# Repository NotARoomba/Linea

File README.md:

<h1 align="center">
  <br>
  
  <br>
  Linea
  <br>
</h1>

<h4 align="center">
Project files for a custom EMR tablet from scratch.

Inspired by [Project Patchouli](https://gitlab.com/yukidama/patchouli).

</h4>

<div align="center">

</div>

<p align="center">
  <a href="#key-features">Key Features</a> •
  <a href="#case-and-cad">Case & CAD</a> •
  <a href="#pcb">PCB</a> •
  <a href="#bom">BOM</a> •
  <a href="#credits">Credits</a> •
  <a href="#license">License</a>
</p>

<!---

--->

## Key Features

- ~500kHz scanning rate
- Large (170x110mm) drawing area
- Bluetooth support (via STM32)
- USB-C for data and charging
- ~~Pen~~ (for another version)

## Case and CAD

The case includes:

- 3D printed parts: a base and a top cover
- Snap-fit case

Designed in Fusion 360.

## PCB

Designed in KiCad. Notable points:

- STM32WB55RGV6TR for bluetooth support
- LiPo battery charging circuit
- USB-C
- 2 ground planes
- FPC touchpad

The PCB has 2 components, the FPC coil grid and the main board.

### FPC

### Main Board

## BOM

| Item         | Price (USD) | Source                                                                                                                                                                                                                                                                                                                                                                                                                                                          |
| ------------ | ----------- | --------------------------------------------------------------------------------------------------------------------------------------------------------------------------------------------------------------------------------------------------------------------------------------------------------------------------------------------------------------------------------------------------------------------------------------------------------------- |
| FPC Board    | 48.67       | JLCPCB                                                                                                                                                                                                                                                                                                                                                                                                                                                          |
| Main Board   | 207.14      | JLCPCB                                                                                                                                                                                                                                                                                                                                                                                                                                                          |
| Test Pen     | 12.35       | [Aliexpress](https://www.aliexpress.com/item/1005001860233195.html?spm=a2g0o.productlist.0.0.111a75d5sBjHGs&mp=1&pdp_npi=5%40dis%21COP%21COP%2077314.30%21COP%2049500.76%21%21COP%2049500.76%21%21%21%40210337bc17525387622585637ecb2a%2112000017887624552%21ct%21CO%216414363499%21%211%210) |
| LiPo 1200mAh | 12.00       | [Online Marketplace](https://articulo.mercadolibre.com.co/MCO-897219547-bateria-37v-1200mah-litio-lipo-35-x-6cm-ancho-05cm-_JM#polycard_client=search-nordic&position=31&search_layout=stack&type=item&tracking_id=64c5a1d6-adab-4203-b581-c1839af5c176&wid=MCO897219547&sid=search)                                                                                                                                                                            |
| **Subtotal** | 280.16      |                                                                                                                                                                                                                                                                                                                                                                                                                                                                 |
| **Shipping** | 30.00       | Estimated                                                                                                                                                                                                                                                                                                                                                                                                                                                       |
| **Total**    | 310.16      |                                                                                                                                                                                                                                                                                                                                                                                                                                                                 |

<!-- https://articulo.mercadolibre.com.co/MCO-568567056-lapiz-repuesto-tabla-digitalizadora-xp-pen-p03-no-wacom-_JM?searchVariation=176600496495#is_advertising=true&searchVariation=176600496495&backend_model=search-backend&position=8&search_layout=stack&type=pad&tracking_id=9f203117-ca3d-40ac-bdf1-dadf37d1ff62&is_advertising=true&ad_domain=VQCATCORE_LST&ad_position=8&ad_click_id=YjFjZWVmY2UtZGUwNi00Y2Y4LTk2NDktMmQ1NjNhZGUyMzNj -->

## Credits

- [Project Patchouli](https://gitlab.com/yukidama/patchouli)
- [Flipper Zero](https://docs.flipper.net/development/hardware)
- Check `/references` for more information

This project uses:

- [KiCad](https://www.kicad.org/)
- [STM32MX](https://www.st.com/en/development-tools/stm32cubemx.html)
- [Fusion 360](https://www.autodesk.com/products/fusion-360/overview)

## You may also like...

- [Niveles De Niveles](https://github.com/NotARoomba/NivelesDeNiveles) – Real-time flood alert app
- [ROCKETMEN](https://github.com/NotARoomba/ROCKETMEN) – Custom flight controller files
- [Tamaki](https://github.com/NotARoomba/Tamaki) – A cute HackPad

## License

MIT

---

> [notaroomba.dev](https://notaroomba.dev) &nbsp;&middot;&nbsp;
> GitHub [@NotARoomba](https://github.com/NotARoomba)

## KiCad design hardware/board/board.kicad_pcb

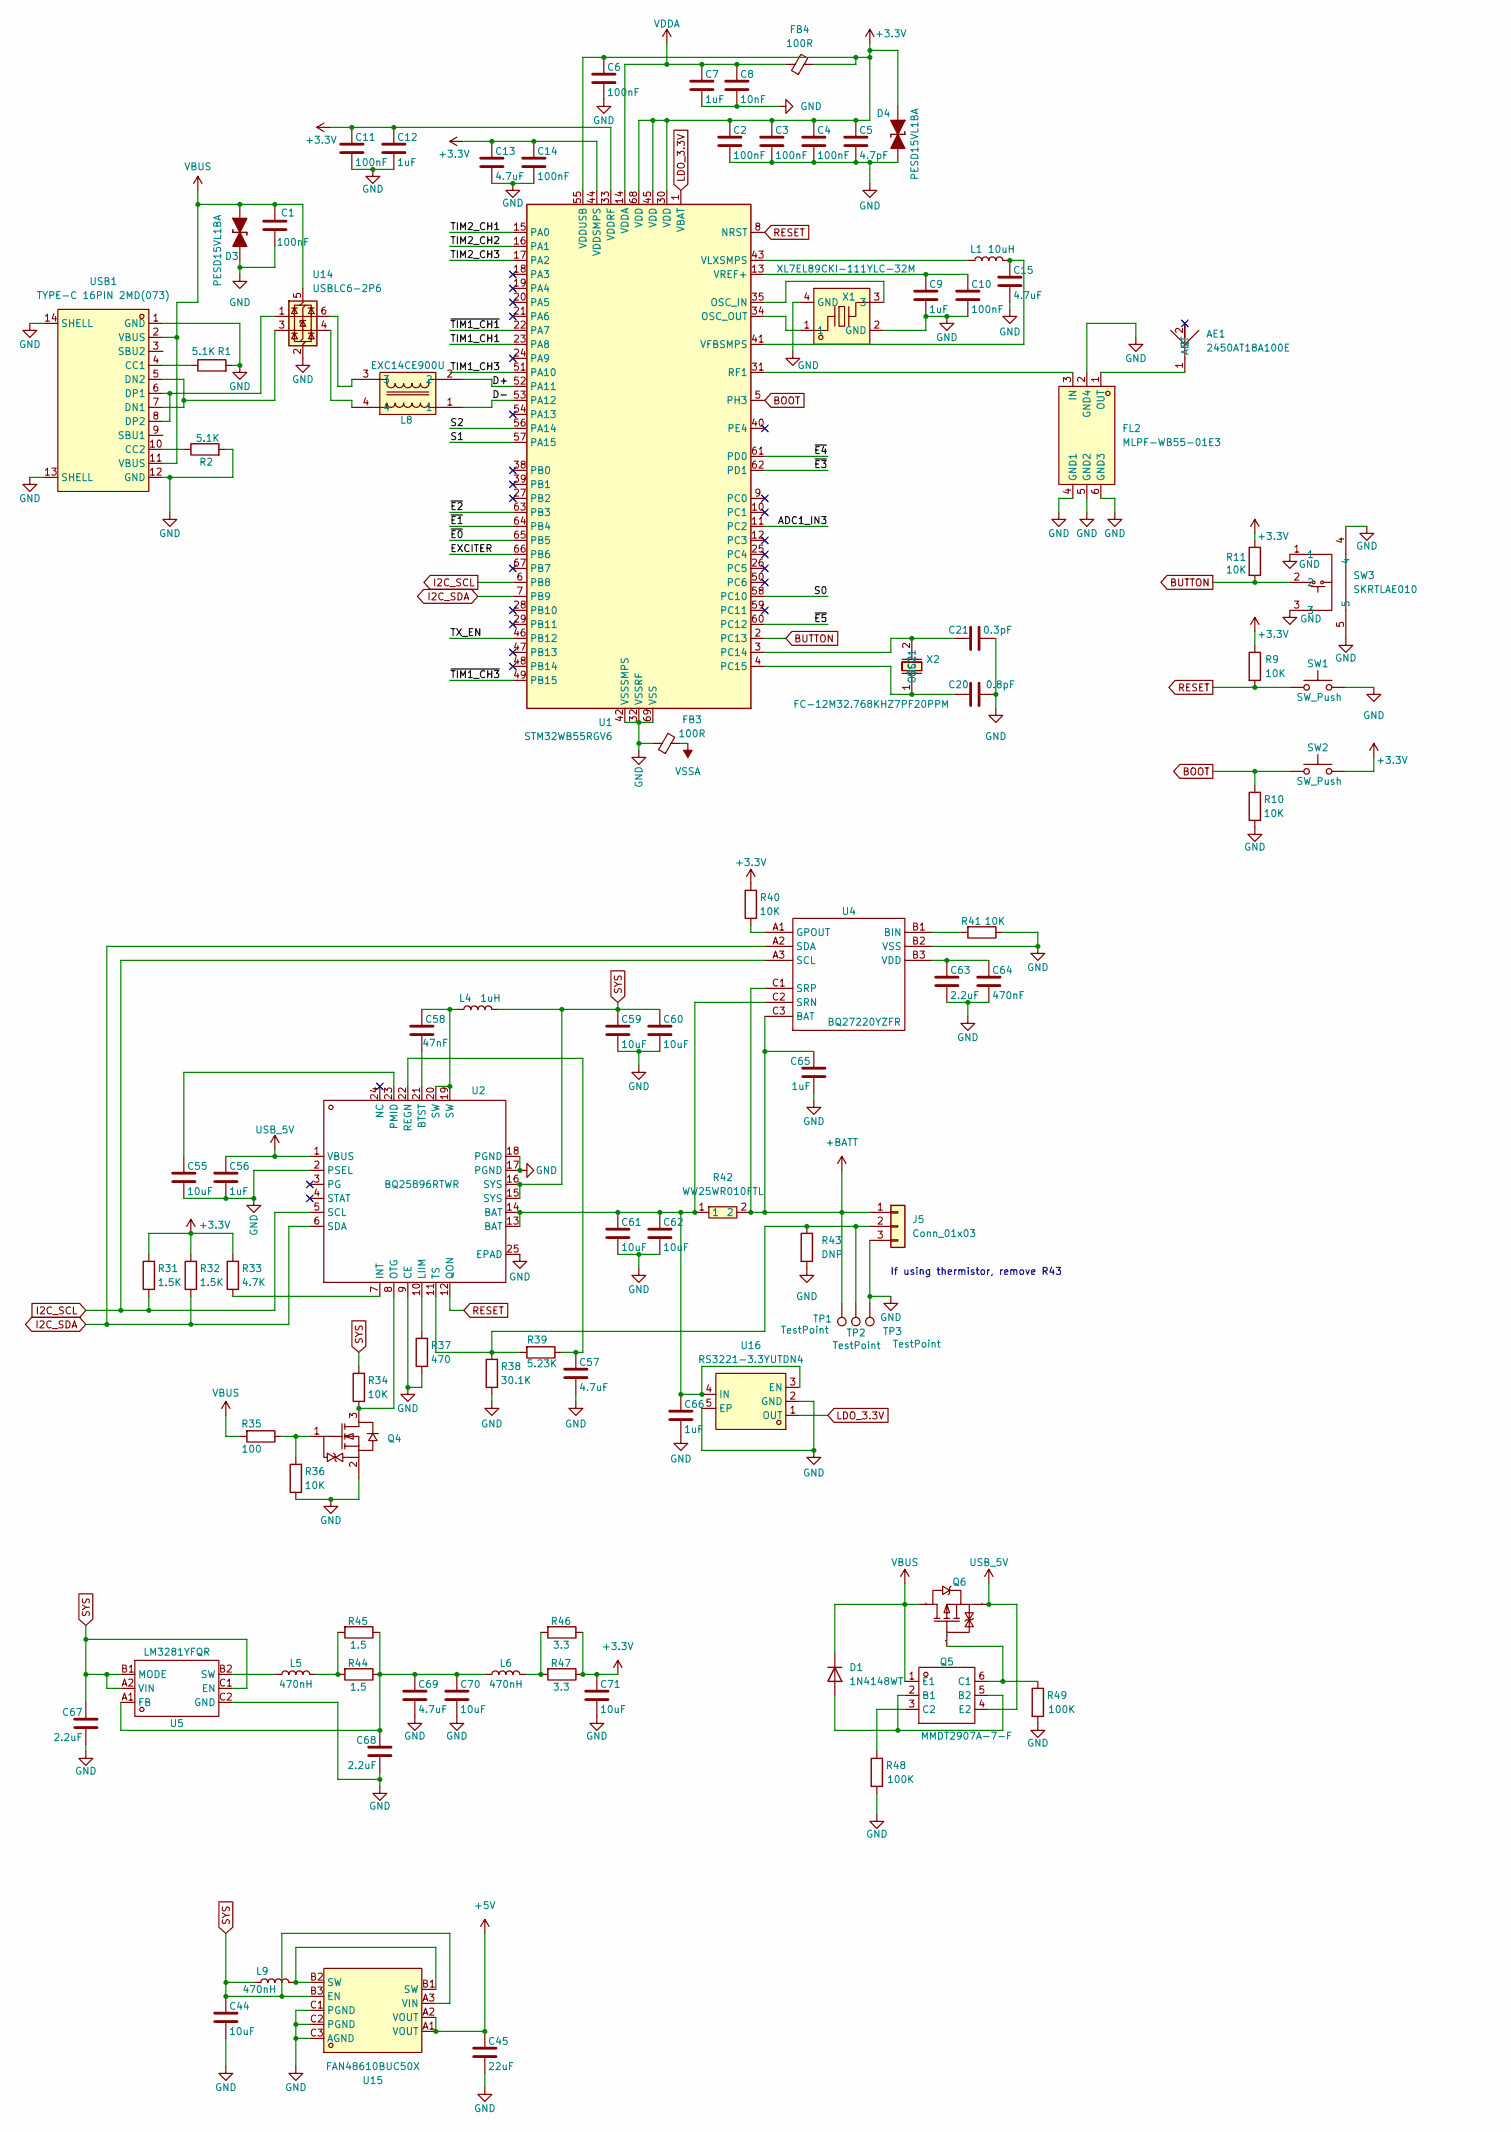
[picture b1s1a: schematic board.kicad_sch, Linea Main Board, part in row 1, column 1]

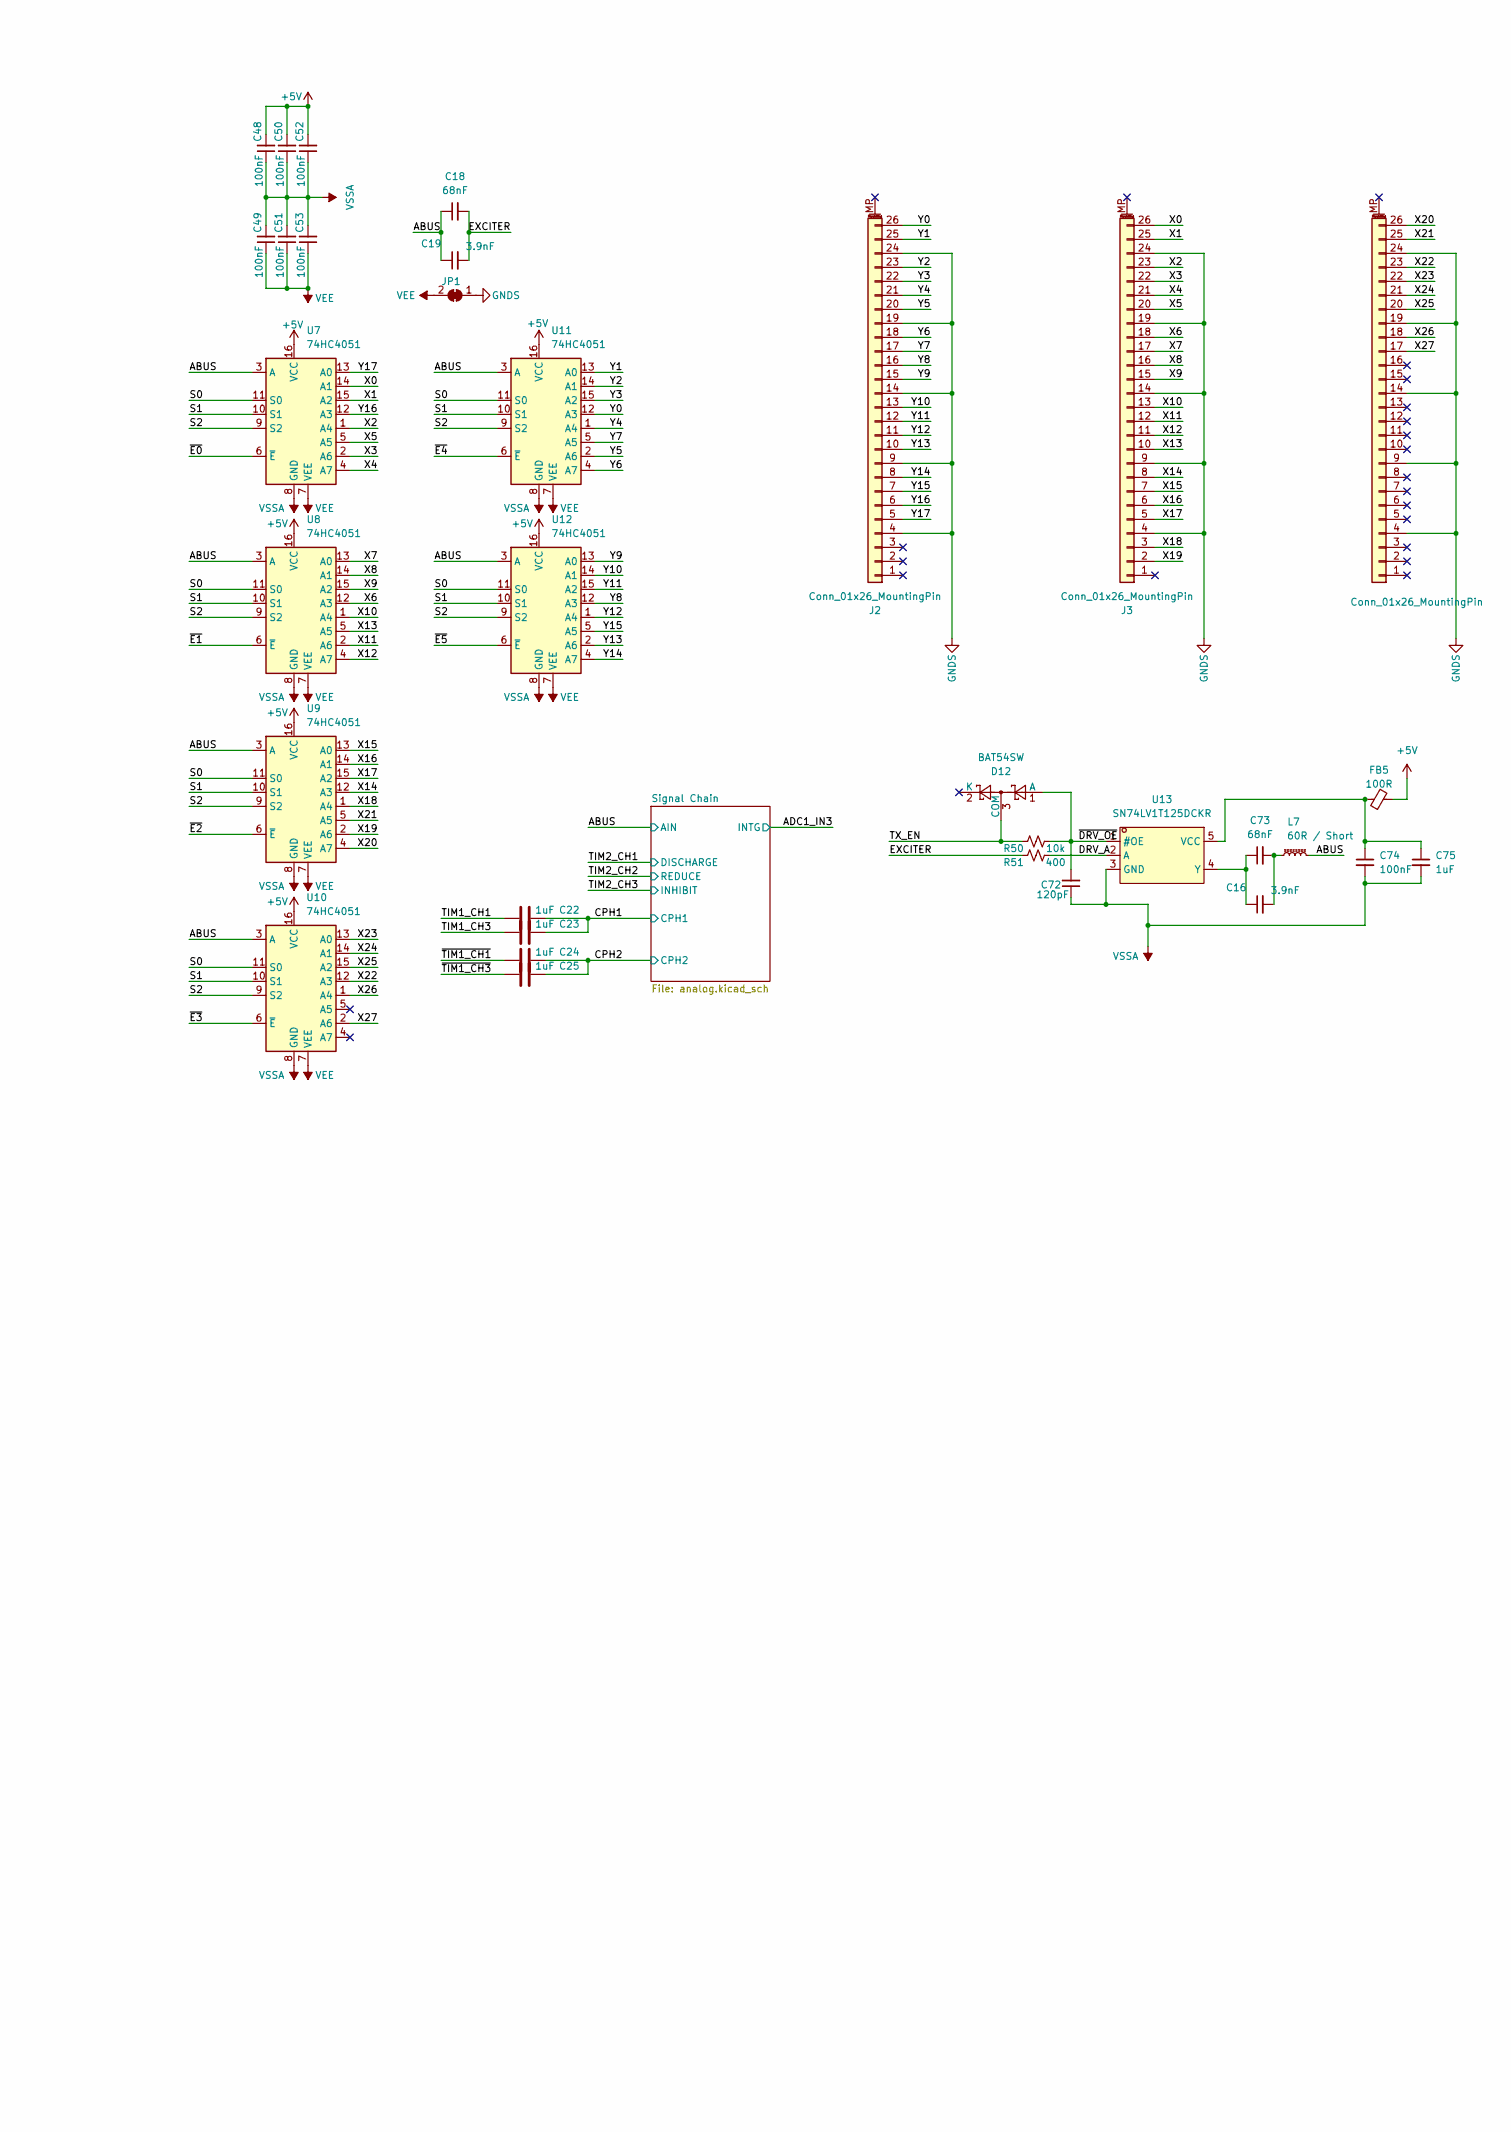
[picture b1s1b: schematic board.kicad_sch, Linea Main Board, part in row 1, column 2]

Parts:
AE1: 2450AT18A100E; ANT-SMD_L3.2-W1.6; LCSC Part C89334
C1, C2, C3, C4, C6, C10, C11, C14, C48, C49, C50, C51, C52, C53, C74: 100nF; C_0402_1005Metric
C5: 4.7pF; C_0402_1005Metric
C7, C9, C12, C22, C23, C24, C25, C56, C65, C66, C75: 1uF; C_0402_1005Metric
C8: 10nF; C_0402_1005Metric
C13, C15, C57, C69: 4.7uF; C_0402_1005Metric
C16, C19: 3.9nF; C_0402_1005Metric
C18, C73: 68nF; C_0402_1005Metric
C20: 0.8pF; C_0402_1005Metric
C21: 0.3pF; C_0402_1005Metric
C44, C55, C59, C60, C61, C62, C70, C71: 10uF; C_0402_1005Metric
C45: 22uF; C_0402_1005Metric
C58: 47nF; C_0402_1005Metric
C63, C67, C68: 2.2uF; C_0402_1005Metric
C64: 470nF; C_0402_1005Metric
C72: 120pF; C_0402_1005Metric
D1: 1N4148WT; D_SOD-523
D3, D4: PESD15VL1BA; D_SOD-323_TVS
D12: BAT54SW; SOT-323_SC-70
FB3, FB4, FB5: 100R; L_0603_1608Metric
FL2: MLPF-WB55-01E3; FILTER-SMD_6P-L1.6-W1.0-P0.50-BL; LCSC Part C2651048
J2, J3, J4: Conn_01x26_MountingPin; Hirose_FH12-26S-0.5SH_1x26-1MP_P0.50mm_Horizontal; LCSC C262277
J5: Conn_01x03; JST_EH_S3B-EH_1x03_P2.50mm_Horizontal; LCSC C263754
JP1: SolderJumper-2_P1.3mm_Bridged_RoundedPad1.0x1.5mm
L1: 10uH; L_0603_1608Metric
L4: 1uH; L_0603_1608Metric
L5, L6: 470nH; L_0603_1608Metric
L7: 60R / Short; L_0603_1608Metric; LCSC C85834
L8: EXC14CE900U; FILTER-SMD_4P-L0.9-W0.7-P0.50-BL; LCSC Part C178761
L9: 470nH; L_Murata_DFE201610P; LCSC C882980
Q4: SOT-523-3_L1.6-W0.8-P1.00-LS1.6-BR; Manufacturer Part DMN313DLT-7; LCSC C155524
Q5: SOT-363_L2.0-W1.3-P0.65-LS2.1-BL; Manufacturer Part MMDT2907A-7-F; LCSC C460232
Q6: SOT-23-3_L2.9-W1.3-P1.90-LS2.4-BR; Manufacturer Part DMP1045U-7; LCSC Part Name 1个P沟道 耐压:12V 电流:4A
R1, R2: 5.1K; R_0402_1005Metric
R9, R10, R11, R34, R36, R40, R41: 10K; R_0402_1005Metric
R31, R32: 1.5K; R_0402_1005Metric
R33: 4.7K; R_0402_1005Metric
R35: 100; R_0402_1005Metric
R37: 470; R_0402_1005Metric
R38: 30.1K; R_0402_1005Metric
R39: 5.23K; R_0402_1005Metric
R42: WW25WR010FTL; R2512; LCSC Part C171418
R43: DNP; R_0402_1005Metric
R44, R45: 1.5; R_0402_1005Metric
R46, R47: 3.3; R_0402_1005Metric
R48, R49: 100K; R_0402_1005Metric
R50: 10k; R_0402_1005Metric
R51: 400; R_0402_1005Metric
SW1, SW2: SW_Push; SW_SPST_CK_RS282G05A3; LCSC C318938
SW3: SKRTLAE010; KEY-SMD_SKRTLAE010; LCSC Part C110293
TP1, TP2, TP3: TestPoint; TestPoint_Pad_1.5x1.5mm
U1: STM32WB55RGV6; QFN-68-1EP_8x8mm_P0.4mm_EP6.4x6.4mm
U2: QFN-24_L4.0-W4.0-P0.50-TL-EP2.7; Manufacturer Part BQ25896RTWR; LCSC C181475
U4: DSBGA-9_L1.7-W1.6-R3-C3-P0.50-BL; Manufacturer Part BQ27220YZFR; LCSC C528617
U5: DSBGA-6_L1.4-W1.1-R3-C2-P0.40-BL; Manufacturer Part LM3281YFQR; LCSC C2070970
U7, U8, U9, U10, U11, U12: 74HC4051; TSSOP-16_4.4x5mm_P0.65mm
U13: SN74LV1T125DCKR; SC-70-5_L2.1-W1.3-P0.65-LS2.1-TL; LCSC Part C75925
U14: USBLC6-2P6; SOT-666
U15: FAN48610BUC50X; WLCSP-9_L1.2-W1.2-R3-C3-P0.40-BL; LCSC Part C890711
U16: RS3221-3.3YUTDN4; UTDFN-4_L1.0-W1.0-P0.63-BL-EP-1; LCSC C2924279
USB1: TYPE-C 16PIN 2MD(073); USB-C-SMD_TYPE-C-6PIN-2MD-073; LCSC Part C2765186
X1: XL7EL89CKI-111YLC-32M; CRYSTAL-SMD_4P-L2.0-W1.6-BL; LCSC Part C2965582
X2: FC-12M32.768KHZ7PF20PPM; FC-12M_L2.0-W1.2; LCSC Part C99009

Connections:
+3.3V: C2.1, C3.1, C4.1, C5.1, C6.1, C11.1, C12.1, C13.1, C14.1, C71.1, D4.2 (A), FB4.2, R9.1, R11.1, R31.2, R32.2, R33.2, R40.2, R46.1, R47.1, SW2.2, U1.30 (VDD), U1.33 (VDDRF), U1.44 (VDDSMPS), U1.45 (VDD), U1.55 (VDDUSB), U1.68 (VDD)
+5V: C45.1, C48.2, C50.2, C52.2, FB5.2, U7.16 (VCC), U8.16 (VCC), U9.16 (VCC), U10.16 (VCC), U11.16 (VCC), U12.16 (VCC), U15.A1 (VOUT), U15.A2 (VOUT)
+BATT: C65.1, J5.1, R42.2, TP1.1, U4.C1 (SRP), U4.C3 (BAT)
/ABUS: C18.1, C19.1, L7.2, U7.3 (A), U8.3 (A), U9.3 (A), U10.3 (A), U11.3 (A), U12.3 (A); also elsewhere on the board
/ADC1_IN3: U1.11 (PC2); also elsewhere on the board
/CPH1: C22.1, C23.1; also elsewhere on the board
/CPH2: C24.1, C25.1; also elsewhere on the board
/D+: L8.2, U1.52 (PA11)
/D-: L8.1, U1.53 (PA12)
/DRV_A: R51.2, U13.2 (A)
/EXCITER: C18.2, C19.2, R51.1, U1.66 (PB6)
/S0: U1.58 (PC10), U7.11 (S0), U8.11 (S0), U9.11 (S0), U10.11 (S0), U11.11 (S0), U12.11 (S0)
/S1: U1.57 (PA15), U7.10 (S1), U8.10 (S1), U9.10 (S1), U10.10 (S1), U11.10 (S1), U12.10 (S1)
/S2: U1.56 (PA14), U7.9 (S2), U8.9 (S2), U9.9 (S2), U10.9 (S2), U11.9 (S2), U12.9 (S2)
/TIM1_CH1: C22.2, U1.23 (PA8)
/TIM1_CH3: C23.2, U1.51 (PA10)
/TIM2_CH1: U1.15 (PA0); also elsewhere on the board
/TIM2_CH2: U1.16 (PA1); also elsewhere on the board
/TIM2_CH3: U1.17 (PA2); also elsewhere on the board
/TX_EN: D12.3 (COM), R50.1, U1.46 (PB12)
/X0: J3.26, U7.14 (A1)
/X1: J3.25, U7.15 (A2)
/X2: J3.23, U7.1 (A4)
/X3: J3.22, U7.2 (A6)
/X4: J3.21, U7.4 (A7)
/X5: J3.20, U7.5 (A5)
/X6: J3.18, U8.12 (A3)
/X7: J3.17, U8.13 (A0)
/X8: J3.16, U8.14 (A1)
/X9: J3.15, U8.15 (A2)
/X10: J3.13, U8.1 (A4)
/X11: J3.12, U8.2 (A6)
/X12: J3.11, U8.4 (A7)
/X13: J3.10, U8.5 (A5)
/X14: J3.8, U9.12 (A3)
/X15: J3.7, U9.13 (A0)
/X16: J3.6, U9.14 (A1)
/X17: J3.5, U9.15 (A2)
/X18: J3.3, U9.1 (A4)
/X19: J3.2, U9.2 (A6)
/X20: J4.26, U9.4 (A7)
/X21: J4.25, U9.5 (A5)
/X22: J4.23, U10.12 (A3)
/X23: J4.22, U10.13 (A0)
/X24: J4.21, U10.14 (A1)
/X25: J4.20, U10.15 (A2)
/X26: J4.18, U10.1 (A4)
/X27: J4.17, U10.2 (A6)
/Y0: J2.26, U11.12 (A3)
/Y1: J2.25, U11.13 (A0)
/Y2: J2.23, U11.14 (A1)
/Y3: J2.22, U11.15 (A2)
/Y4: J2.21, U11.1 (A4)
/Y5: J2.20, U11.2 (A6)
/Y6: J2.18, U11.4 (A7)
/Y7: J2.17, U11.5 (A5)
/Y8: J2.16, U12.12 (A3)
/Y9: J2.15, U12.13 (A0)
/Y10: J2.13, U12.14 (A1)
/Y11: J2.12, U12.15 (A2)
/Y12: J2.11, U12.1 (A4)
/Y13: J2.10, U12.2 (A6)
/Y14: J2.8, U12.4 (A7)
/Y15: J2.7, U12.5 (A5)
/Y16: J2.6, U7.12 (A3)
/Y17: J2.5, U7.13 (A0)
/~DRV_OE: C72.2, D12.1 (A), R50.2, U13.1 (#OE)
/~E0: U1.65 (PB5), U7.6 (~E)
/~E1: U1.64 (PB4), U8.6 (~E)
/~E2: U1.63 (PB3), U9.6 (~E)
/~E3: U1.62 (PD1), U10.6 (~E)
/~E4: U1.61 (PD0), U11.6 (~E)
/~E5: U1.60 (PC12), U12.6 (~E)
/~TIM1_CH1: C24.2, U1.22 (PA7)
/~TIM1_CH3: C25.2, U1.49 (PB15)
BOOT: R10.2, SW2.1, U1.5 (PH3)
BUTTON: R11.2, SW3.2, U1.2 (PC13)
GND: C1.2, C2.2, C3.2, C4.2, C5.2, C6.2, C7.2, C8.2, C9.2, C10.2, C11.2, C12.2, C13.2, C14.2, C15.2, C20.2, C21.2, C44.2, C45.2, C55.2, C56.2, C57.2, C59.2, C60.2, C61.2, C62.2, C63.2, C64.2, C65.2, C66.2, C67.2, C68.2, C69.2, C70.2, C71.2, D3.1 (K), D4.1 (K), FB3.1, FL2.2 (GND4), FL2.4 (GND1), FL2.5 (GND2), FL2.6 (GND3), J5.3, Q4.2 (S), R1.2, R2.2, R10.1, R36.1, R37.1, R38.1, R41.1, R43.2, R48.2, R49.2, SW1.2, SW3.1, SW3.3, SW3.4, SW3.5, TP3.1, U1.32 (VSSRF), U1.42 (VSSSMPS), U1.69 (VSS), U2.2 (PSEL), U2.9 (CE), U2.17 (PGND), U2.18 (PGND), U2.25 (EPAD), U4.B2 (VSS), U5.C2 (GND), U14.2 (GND), U15.C1 (PGND), U15.C2 (PGND), U15.C3 (AGND), U16.2 (GND), U16.5 (EP), USB1.1 (GND), USB1.12 (GND), USB1.13 (SHELL), USB1.14 (SHELL), X1.2 (GND), X1.4 (GND); also elsewhere on the board
GNDS: J2.4, J2.9, J2.14, J2.19, J2.24, J3.4, J3.9, J3.14, J3.19, J3.24, J4.4, J4.9, J4.14, J4.19, J4.24, JP1.1 (A)
I2C_SCL: R31.1, U1.6 (PB8), U2.5 (SCL), U4.A3 (SCL)
I2C_SDA: R32.1, U1.7 (PB9), U2.6 (SDA), U4.A2 (SDA)
LDO_3.3V: U1.1 (VBAT), U16.1 (OUT)
unnamed: AE1.1 (ANT), FL2.1 (OUT)
unnamed: C16.2, C73.2, L7.1
unnamed: C58.1, L4.1, U2.19 (SW), U2.20 (SW)
unnamed: D1.2 (A), Q5.2 (B1), Q5.5 (B2)
unnamed: FL2.3 (IN), U1.31 (RF1)
unnamed: J5.2, R38.2, R39.2, R43.1, TP2.1, U2.11 (TS)
unnamed: L5.2, R44.2, R45.2
unnamed: L6.2, R46.2, R47.2
unnamed: L8.3, U14.6 (I/O1)
unnamed: L8.4, U14.4 (I/O2)
unnamed: L9.2, U15.B1 (SW), U15.B2 (SW)
unnamed: Q4.3 (D), R34.1, U2.8 (OTG)
unnamed: Q4.1 (G), R35.1, R36.2
unnamed: Q5.6 (C1), Q6.1 (G), R49.1
unnamed: Q5.3 (C2), R48.1
unnamed: U1.35 (OSC_IN), X1.3
unnamed: U1.34 (OSC_OUT), X1.1
unnamed: C21.1, U1.3 (PC14), X2.2 (OSC2)
unnamed: C20.1, U1.4 (PC15), X2.1 (OSC1)
unnamed: C15.1, L1.2, U1.41 (VFBSMPS)
unnamed: L1.1, U1.43 (VLXSMPS)
unnamed: C9.1, C10.1, U1.13 (VREF+)
unnamed: C58.2, U2.21 (BTST)
unnamed: R33.1, U2.7 (INT)
unnamed: R37.2, U2.10 (LIIM)
unnamed: C55.1, U2.23 (PMID)
unnamed: C57.1, R39.1, U2.22 (REGN)
unnamed: R41.2, U4.B1 (BIN)
unnamed: R40.1, U4.A1 (GPOUT)
unnamed: C63.1, C64.1, U4.B3 (VDD)
unnamed: C68.1, C69.1, C70.1, L6.1, R44.1, R45.1, U5.A1 (FB)
unnamed: L5.1, U5.B2 (SW)
unnamed: C74.1, C75.1, FB5.1, U13.5 (VCC)
unnamed: C16.1, C73.1, U13.4 (Y)
unnamed: C61.1, C62.1, C66.1, R42.1, U2.13 (BAT), U2.14 (BAT), U4.C2 (SRN), U16.3 (EN), U16.4 (IN)
unnamed: R1.1, USB1.4 (CC1)
unnamed: R2.1, USB1.10 (CC2)
unnamed: U14.3 (I/O2), USB1.5 (DN2), USB1.7 (DN1)
unnamed: U14.1 (I/O1), USB1.6 (DP1), USB1.8 (DP2)
RESET: R9.2, SW1.1, U1.8 (NRST), U2.12 (QON)
SYS: C44.1, C59.1, C60.1, C67.1, L4.2, L9.1, R34.2, U2.15 (SYS), U2.16 (SYS), U5.A2 (VIN), U5.B1 (MODE), U5.C1 (EN), U15.A3 (VIN), U15.B3 (EN)
USB_5V: C56.1, Q5.4 (E2), Q6.2 (S), U2.1 (VBUS)
VBUS: C1.1, D1.1 (K), D3.2 (A), Q5.1 (E1), Q6.3 (D), R35.2, U14.5 (VBUS), USB1.2 (VBUS), USB1.11 (VBUS)
VDDA: C7.1, C8.1, FB4.1, U1.14 (VDDA); also elsewhere on the board
VEE: C49.1, C51.1, C53.1, JP1.2 (B), U7.7 (VEE), U8.7 (VEE), U9.7 (VEE), U10.7 (VEE), U11.7 (VEE), U12.7 (VEE); also elsewhere on the board
VSSA: C48.1, C49.2, C50.1, C51.2, C52.1, C53.2, C72.1, C74.2, C75.2, FB3.2, U7.8 (GND), U8.8 (GND), U9.8 (GND), U10.8 (GND), U11.8 (GND), U12.8 (GND), U13.3 (GND); also elsewhere on the board

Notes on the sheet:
If using thermistor, remove R43

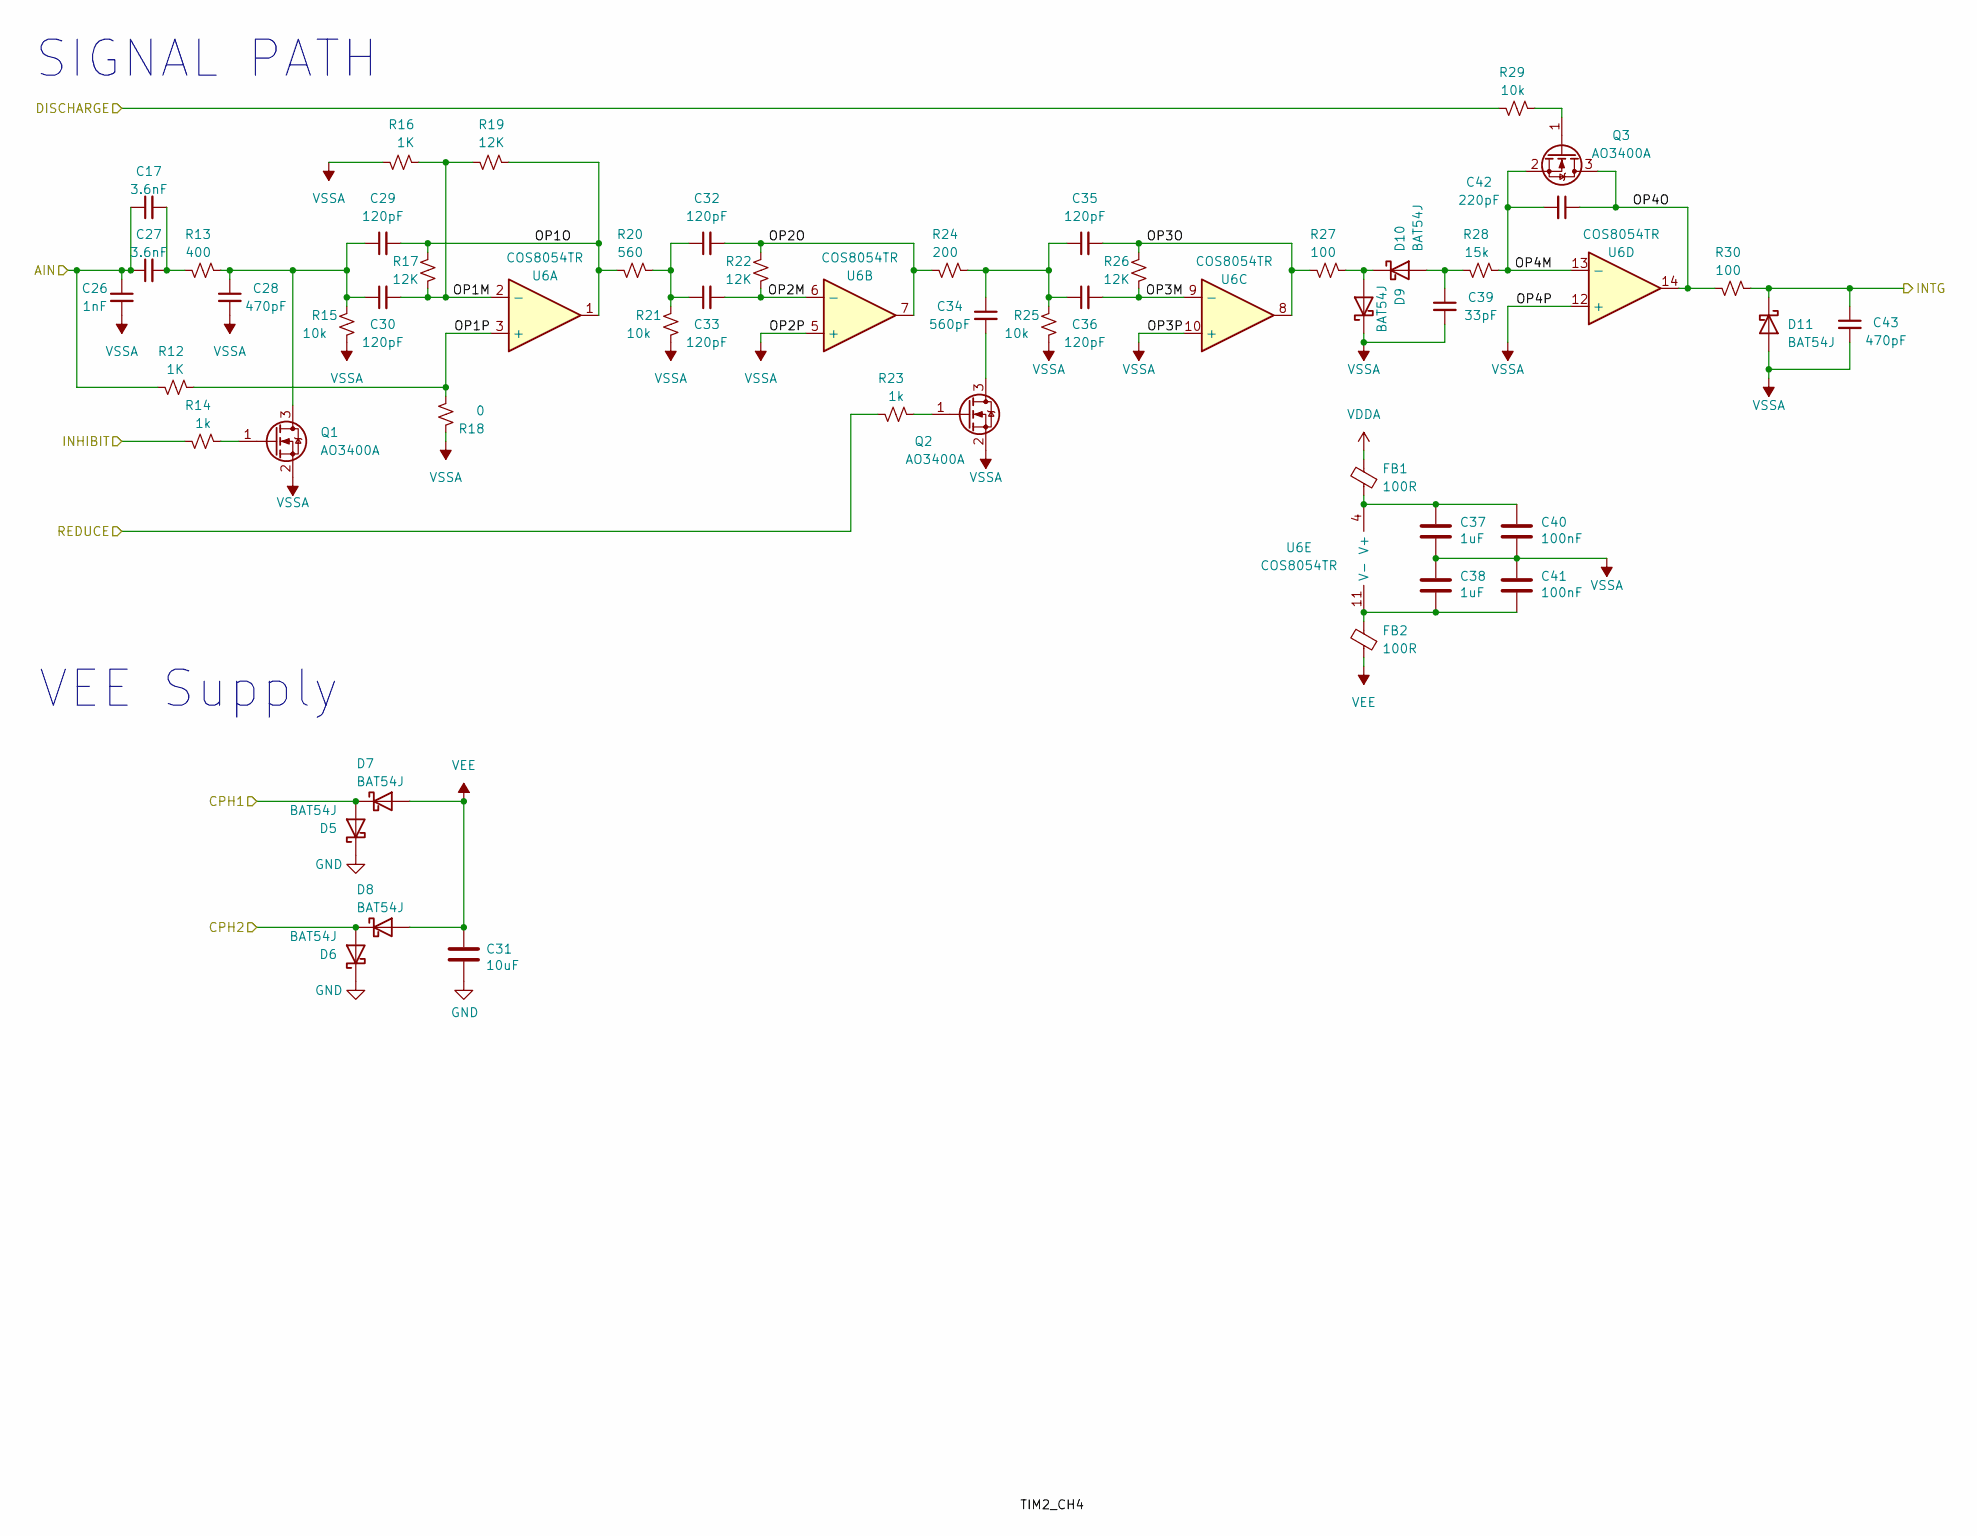
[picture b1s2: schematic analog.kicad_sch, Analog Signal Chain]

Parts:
C17, C27: 3.6nF; C_0603_1608Metric
C26: 1nF; C_0402_1005Metric
C28, C43: 470pF; C_0402_1005Metric
C29, C30, C32, C33, C35, C36: 120pF; C_0402_1005Metric
C31: 10uF; C_0402_1005Metric
C34: 560pF; C_0402_1005Metric
C37, C38: 1uF; C_0603_1608Metric
C39: 33pF; C_0402_1005Metric
C40, C41: 100nF; C_0603_1608Metric
C42: 220pF; C_0402_1005Metric
D5, D6, D7, D8, D9, D10, D11: BAT54J; D_SOD-323F
FB1, FB2: 100R; L_0603_1608Metric
Q1, Q2, Q3: AO3400A; SOT-23
R12, R16: 1K; R_0402_1005Metric
R13: 400; R_0402_1005Metric
R14, R23: 1k; R_0402_1005Metric
R15, R21, R25, R29: 10k; R_0402_1005Metric
R17, R19, R22, R26: 12K; R_0402_1005Metric
R18: 0; R_0402_1005Metric
R20: 560; R_0402_1005Metric
R24: 200; R_0402_1005Metric
R27, R30: 100; R_0402_1005Metric
R28: 15k; R_0402_1005Metric
U6: COS8054TR; TSSOP-14_4.4x5mm_P0.65mm

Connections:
/ABUS: C17.1, C26.1, C27.1, R12.1; also elsewhere on the board
/ADC1_IN3: C43.1, D11.1 (K), R30.2; also elsewhere on the board
/CPH1: D5.2 (A), D7.1 (K); also elsewhere on the board
/CPH2: D6.2 (A), D8.1 (K); also elsewhere on the board
/Signal Chain/OP1M: C30.2, R16.2, R17.1, R19.1, U6.2 (-)
/Signal Chain/OP1O: C29.2, R17.2, R19.2, R20.1, U6.1
/Signal Chain/OP1P: R12.2, R18.1, U6.3 (+)
/Signal Chain/OP2M: C33.2, R22.1, U6.6 (-)
/Signal Chain/OP2O: C32.2, R22.2, R24.1, U6.7
/Signal Chain/OP3M: C36.2, R26.1, U6.9 (-)
/Signal Chain/OP3O: C35.2, R26.2, R27.1, U6.8
/Signal Chain/OP4M: C42.2, Q3.2 (S), R28.2, U6.13 (-)
/Signal Chain/OP4O: C42.1, Q3.3 (D), R30.1, U6.14
/TIM2_CH1: R29.1; also elsewhere on the board
/TIM2_CH2: R23.1; also elsewhere on the board
/TIM2_CH3: R14.1; also elsewhere on the board
GND: C31.2, D5.1 (K), D6.1 (K); also elsewhere on the board
unnamed: C17.2, C27.2, R13.1
unnamed: C32.1, C33.1, R20.2, R21.2
unnamed: C34.1, C35.1, C36.1, R24.2, R25.2
unnamed: C39.1, D10.2 (A), R28.1
unnamed: D9.2 (A), D10.1 (K), R27.2
unnamed: C28.1, C29.1, C30.1, Q1.3 (D), R13.2, R15.2
unnamed: Q1.1 (G), R14.2
unnamed: C34.2, Q2.3 (D)
unnamed: Q2.1 (G), R23.2
unnamed: Q3.1 (G), R29.2
unnamed: C37.1, C40.1, FB1.1, U6.4 (V+)
unnamed: C38.2, C41.2, FB2.2, U6.11 (V-)
VDDA: FB1.2; also elsewhere on the board
VEE: C31.1, D7.2 (A), D8.2 (A), FB2.1; also elsewhere on the board
VSSA: C26.2, C28.2, C37.2, C38.1, C39.2, C40.2, C41.1, C43.2, D9.1 (K), D11.2 (A), Q1.2 (S), Q2.2 (S), R15.1, R16.1, R18.2, R21.1, R25.1, U6.5 (+), U6.10 (+), U6.12 (+); also elsewhere on the board

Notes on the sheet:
SIGNAL PATH
VEE Supply

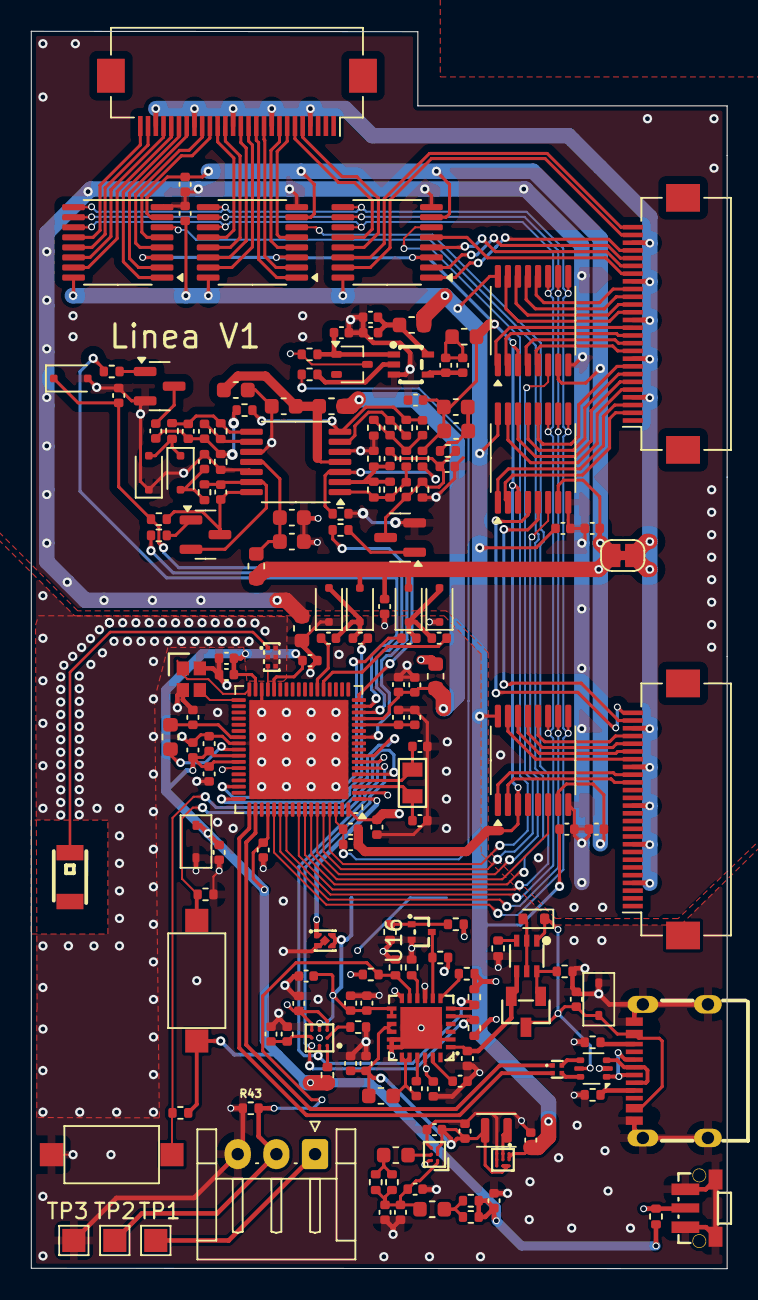
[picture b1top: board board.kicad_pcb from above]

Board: 4 copper layers, 45.0 x 80.0 mm, 177 parts (1 on the bottom side), 149 nets.

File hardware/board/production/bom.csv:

Designator,Footprint,Quantity,Value,LCSC Part #
AE1,ANT-SMD_L3.2-W1.6,1,2450AT18A100E,C89334
"C1, C10, C11, C14, C2, C3, C4, C48, C49, C50, C51, C52, C53, C6, C74",0402,15,100nF,
"C12, C22, C23, C24, C25, C56, C65, C66, C7, C75, C9",0402,11,1uF,
"C13, C15, C57, C69",0402,4,4.7uF,
"C16, C19",0402,2,3.9nF,
"C17, C27",0603,2,3.6nF,
"C18, C73",0402,2,68nF,
C20,0402,1,0.8pF,
C21,0402,1,0.3pF,
C26,0402,1,1nF,
"C28, C43",0402,2,470pF,
"C29, C30, C32, C33, C35, C36, C72",0402,7,120pF,
"C31, C44, C55, C59, C60, C61, C62, C70, C71",0402,9,10uF,
C34,0402,1,560pF,
"C37, C38",0603,2,1uF,
C39,0402,1,33pF,
"C40, C41",0603,2,100nF,
C42,0402,1,220pF,
C45,0402,1,22uF,
C5,0402,1,4.7pF,
C58,0402,1,47nF,
"C63, C67, C68",0402,3,2.2uF,
C64,0402,1,470nF,
C8,0402,1,10nF,
D1,D_SOD-523,1,1N4148WT,
"D10, D11, D5, D6, D7, D8, D9",D_SOD-323F,7,BAT54J,
D12,SOT-323_SC-70,1,BAT54SW,
"D3, D4",D_SOD-323_TVS,2,PESD15VL1BA,
"FB1, FB2, FB3, FB4, FB5",0603,5,100R,
FL2,FILTER-SMD_6P-L1.6-W1.0-P0.50-BL,1,MLPF-WB55-01E3,C2651048
"J2, J3, J4",Hirose_FH12-26S-0.5SH_1x26-1MP_P0.50mm_Horizontal,3,Conn_01x26_MountingPin,C262277
J5,JST_EH_S3B-EH_1x03_P2.50mm_Horizontal,1,Conn_01x03,C263754
JP1,SolderJumper-2_P1.3mm_Bridged_RoundedPad1.0x1.5mm,1,~,
L1,0603,1,10uH,
L4,0603,1,1uH,
"L5, L6",0603,2,470nH,
L7,0603,1,60R / Short, C85834
L8,FILTER-SMD_4P-L0.9-W0.7-P0.50-BL,1,EXC14CE900U,C178761
L9,L_Murata_DFE201610P,1,470nH,
"Q1, Q2, Q3",SOT-23,3,AO3400A,
Q4,SOT-523-3_L1.6-W0.8-P1.00-LS1.6-BR,1,~,
Q5,SOT-363_L2.0-W1.3-P0.65-LS2.1-BL,1,~,C460232
Q6,SOT-23-3_L2.9-W1.3-P1.90-LS2.4-BR,1,~,C177033
"R1, R2",0402,2,5.1K,
"R10, R11, R15, R21, R25, R29, R34, R36, R40, R41, R50, R9",0402,12,10K,
"R12, R14, R16, R23",0402,4,1K,
"R13, R51",0402,2,400,
"R17, R19, R22, R26",0402,4,12K,
R18,0402,1,0,
R20,0402,1,560,
R24,0402,1,200,
"R27, R30, R35",0402,3,100,
R28,0402,1,15k,
"R31, R32",0402,2,1.5K,
R33,0402,1,4.7K,
R37,0402,1,470,
R38,0402,1,30.1K,
R39,0402,1,5.23K,
R42,0402,1,10m,
R43,0402,1,DNP,
"R44, R45",0402,2,1.5,
"R46, R47",0402,2,3.3,
"R48, R49",0402,2,100K,
"SW1, SW2",SW_SPST_CK_RS282G05A3,2,SW_Push,C318938
SW3,KEY-SMD_SKRTLAE010,1,SKRTLAE010,C110293
"TP1, TP2, TP3",TestPoint_Pad_1.5x1.5mm,3,TestPoint,
U1,QFN-68-1EP_8x8mm_P0.4mm_EP6.4x6.4mm,1,STM32WB55RGV6,
"U10, U11, U12, U7, U8, U9",TSSOP-16_4.4x5mm_P0.65mm,6,74HC4051,
U13,SC-70-5_L2.1-W1.3-P0.65-LS2.1-TL,1,SN74LV1T125DCKR,C75925
U14,SOT-666,1,USBLC6-2P6,
U15,WLCSP-9_L1.2-W1.2-R3-C3-P0.40-BL,1,FAN48610BUC50X,C890711
U16,UTDFN-4_L1.0-W1.0-P0.63-BL-EP-1,1,RS3221-3.3YUTDN4,C2924279
U2,QFN-24_L4.0-W4.0-P0.50-TL-EP2.7,1,~,
U4,DSBGA-9_L1.7-W1.6-R3-C3-P0.50-BL,1,~,C528617
U5,DSBGA-6_L1.4-W1.1-R3-C2-P0.40-BL,1,~,C2070970
U6,TSSOP-14_4.4x5mm_P0.65mm,1,COS8054TR,
USB1,USB-C-SMD_TYPE-C-6PIN-2MD-073,1,TYPE-C 16PIN 2MD(073),C2765186
X1,CRYSTAL-SMD_4P-L2.0-W1.6-BL,1,XL7EL89CKI-111YLC-32M,C2965582
X2,FC-12M_L2.0-W1.2,1,FC-12M32.768KHZ7PF20PPM,C99009

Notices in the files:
firmware/Core/Src/tim.c:
Copyright (c) 2025 STMicroelectronics.
All rights reserved.
This software is licensed under terms that can be found in the LICENSE file
